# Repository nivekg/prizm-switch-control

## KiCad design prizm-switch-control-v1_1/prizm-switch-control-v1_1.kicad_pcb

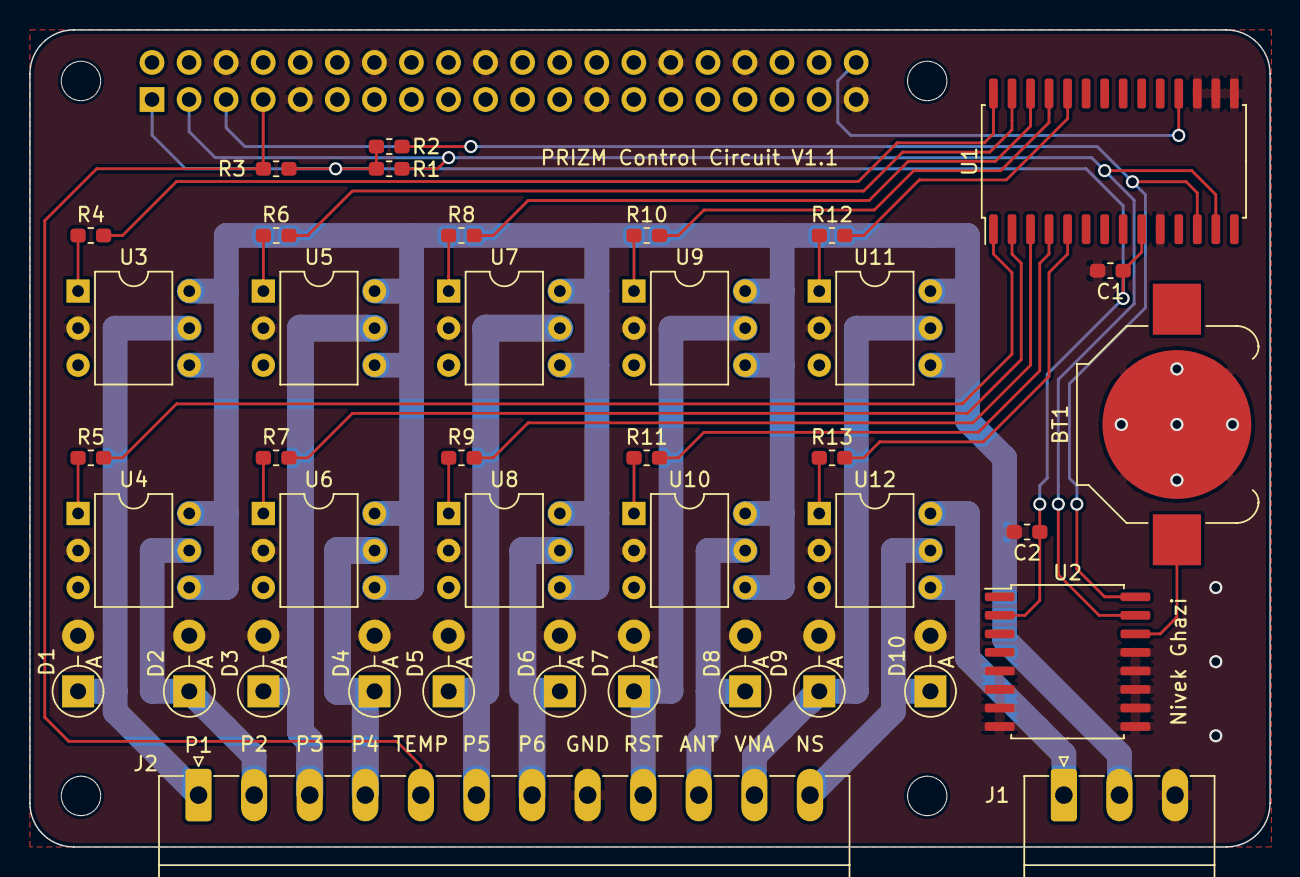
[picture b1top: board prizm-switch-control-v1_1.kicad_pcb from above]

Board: 2 copper layers, 85.0 x 56.0 mm, 45 parts (1 on the bottom side), 39 nets.

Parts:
BT1: V3; BatteryHolder_Keystone_3000_1x12mm
C1: C; C_0603_1608Metric_Pad1.05x0.95mm_HandSolder
C2: 1uF; C_0603_1608Metric_Pad1.05x0.95mm_HandSolder
D1, D2, D3, D4, D5, D6, D7, D8, D9, D10: 1N4001; D_DO-41_SOD81_P3.81mm_Vertical_AnodeUp
J1: Power Connector; PhoenixContact_MC_1,5_3-G-3.81_1x03_P3.81mm_Horizontal
J2: Frontend Connector; PhoenixContact_MC_1,5_12-G-3.81_1x12_P3.81mm_Horizontal
MK1, MK2, MK3, MK4: M2.5; MountingHole_2.7mm_M2.5
P1: RPi-Header; PinSocket_2x20_P2.54mm_Vertical
R1, R2, R3: 4K7; R_0603_1608Metric_Pad1.05x0.95mm_HandSolder
R4, R5, R6, R7, R8, R9, R10, R11, R12, R13: 200; R_0603_1608Metric_Pad1.05x0.95mm_HandSolder
U1: MCP23017_SO; SOIC-28W_7.5x17.9mm_P1.27mm
U2: DS3231M; SOIC-16W_7.5x10.3mm_P1.27mm
U3, U4, U5, U6, U7, U8, U9, U10, U11, U12: TLP3543; DIP-6_W7.62mm

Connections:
+3V3: C1.1, C2.1, P1.1, R1.1, R2.1, R3.1, U1.9, U2.2
+12V: J1.2, U3.4, U3.6, U4.4, U4.6, U5.4, U5.6, U6.4, U6.6, U7.4, U7.6, U8.4, U8.6, U9.4, U9.6, U10.4, U10.6, U11.4, U11.6
+15V: J1.1, U12.4, U12.6
/i2c_expander/I2C_SCL: P1.5, R2.2, U1.12, U2.16
/i2c_expander/I2C_SDA: P1.3, R1.2, U1.13, U2.15
/i2c_expander/NOISE_ON: R13.2, U1.5
/i2c_expander/S1_POS_1: R4.2, U1.28
/i2c_expander/S1_POS_2: R5.2, U1.1
/i2c_expander/S1_POS_3: R6.2, U1.27
/i2c_expander/S1_POS_4: R7.2, U1.2
/i2c_expander/S1_POS_5: R8.2, U1.26
/i2c_expander/S1_POS_6: R9.2, U1.3
/i2c_expander/S1_RESET: R10.2, U1.25
/i2c_expander/S2_POS_1: R11.2, U1.4
/i2c_expander/S2_POS_2: R12.2, U1.24
/i2c_expander/~RESET: P1.40, U1.18
/output_connectors/ANTENNA: D8.1, J2.10, U10.5
/output_connectors/NOISE-SOURCE: D10.1, J2.12, U12.5
/output_connectors/ONE-WIRE: J2.5, P1.7, R3.2
/output_connectors/POS_1: D1.1, J2.1, U3.5
/output_connectors/POS_2: D2.1, J2.2, U4.5
/output_connectors/POS_3: D3.1, J2.3, U5.5
/output_connectors/POS_4: D4.1, J2.4, U6.5
/output_connectors/POS_5: D5.1, J2.6, U7.5
/output_connectors/POS_6: D6.1, J2.7, U8.5
/output_connectors/RESET: D7.1, J2.9, U9.5
/output_connectors/VNA: D9.1, J2.11, U11.5
/real_time_clock/3.3V_Backup: BT1.1, U2.14
GND: BT1.2, C1.2, C2.2, D1.2, D2.2, D3.2, D4.2, D5.2, D6.2, D7.2, D8.2, D9.2, D10.2, J1.3, J2.8, P1.6, P1.9, P1.14, P1.20, P1.25, P1.30, P1.34, P1.39, U1.10, U1.15, U1.16, U1.17, U2.5, U2.6, U2.7, U2.8, U2.9, U2.10, U2.11, U2.12, U2.13, U3.2, U4.2, U5.2, U6.2, U7.2, U8.2, U9.2, U10.2, U11.2, U12.2
unnamed: R4.1, U3.1
unnamed: R5.1, U4.1
unnamed: R6.1, U5.1
unnamed: R7.1, U6.1
unnamed: R8.1, U7.1
unnamed: R9.1, U8.1
unnamed: R10.1, U9.1
unnamed: R11.1, U10.1
unnamed: R12.1, U11.1
unnamed: R13.1, U12.1

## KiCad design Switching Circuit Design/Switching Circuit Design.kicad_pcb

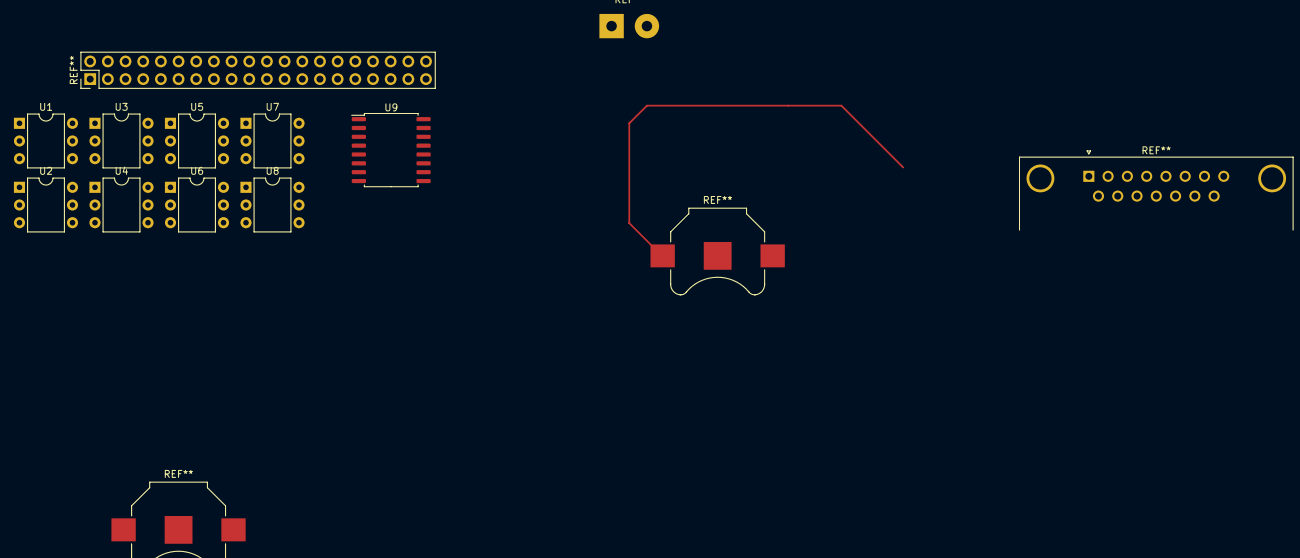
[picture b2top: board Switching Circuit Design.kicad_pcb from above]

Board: 2 copper layers, 9 parts (0 on the bottom side), 9 nets.

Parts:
U1, U2, U3, U4, U5, U6, U7, U8: TLP3543; DIP-6_W7.62mm
U9: DS3231M; SOIC-16W_7.5x10.3mm_P1.27mm

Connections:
3.3V: U1.2, U1.5, U2.2, U2.5, U3.2, U3.5, U4.2, U5.2, U5.5, U6.2, U6.5, U7.2, U7.5, U8.2, U8.5, U9.5, U9.6, U9.7, U9.8, U9.9, U9.10, U9.11, U9.12, U9.13
Drain1: U7.4, U7.6
Drain2: U3.4, U3.6
Drain3: U6.4, U6.6
Drain4: U2.4, U2.6
Drain5: U5.4, U5.6
Drain6: U8.4, U8.6
Drain7: U1.4, U1.6
Drain8: U4.4, U4.6

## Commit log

2019-06-19 Add files via upload
    New switching circuit
2019-06-25 updated switch control schematic and partial board layout
2019-06-26 Add files via upload
    Updated PCB
2019-06-26 Further updated PCB
2019-06-27 Final board layout
2019-06-27 Added gerber files and names
2019-06-29 fixed unrouted nets and generated gerber files for fabrication
2019-07-02 rename gerbers.zip
2019-07-08 Fixed error where optoisolators output was connected in reverse
2019-07-08 generated new gerbers to take in account that optoisolator output was reversed
2019-09-18 Added pullup resistor for one-wire interface and changed 13 pin connector to 12 pin
2019-10-07 Final verision of schematic and PCB layout
2019-12-01 final version
2020-02-11 Updated to control second frontend switch
2020-02-11 Added connector pin labels
2020-02-11 Gerber files for pcbway
2020-03-06 Fixed ERC and DRC errors
2020-03-06 Removed generatable files
2020-03-06 Moved all files from switch-control-hat to root
2020-03-06 Added MFN, MPN, VN and VPN fields for all symbols
2020-03-06 Moved design to its version folder
